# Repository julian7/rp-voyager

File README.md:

# Voyager keyboard with RP2354A

This repository contains the necessary files for manufacturing of a split keyboard with on-board RP2354A microcontroller.

Features:

- On-board RP2354A MCU (2MB flash) for each side
- USB-C connection for power, firmware update, and a separate USB-C for UART connection between the halves
- RGB matrix under each key
- Gateron KS-33 / Kailh Choc v1 / Kailh Choc v2 low-profile keyswitches
- 1.2mm top plate (mainly planning for KS-33)
- FreeCAD design for case and plate
- ZMK firmware with local build

Non-features:

- Wireless functionality
- No tooling for mass production beyond common PCB prototyping and hobbyist CNC/3D print.

## What is Voyager?

Voyager is a minimal, split keyboard by [ZSA Technology Labs](https://www.zsa.io/), the same company who was behind the now discontinued Planck EZ.

The original Voyager is using an STM32 MCU, with RGB matrix. It has 52 keys, and 52 LEDs.

## Project status

Experimental build is done:

Electronics are working well, but LED power consumption can exceed available resources. Please be aware that higher LED brightness settings can crash the firmware.

## Change notes

Version v1.0 has been built, but the left side is not usable:

- ROW0-ROW3 are not connected to the MCU
- missing trace between CONN_TX test pad and the side USB recepticle's TX line

The right side can be put to work, with a single design flaw:

- The eFuse is always disabled. As a solution, put a 1 MΩ resistor (I've used a 0805 package, but probably a 0603 would be better) between pin 1 and pin 2 of Q1 MOSFET.

In general, LED silk screen markings were unreadable, and the ones I've purchased had different pin numbering. I've placed them by following the traces instead.

As a minor detail, SMD encoders' holes are a bit too tight, a 0.1mm clearance is added. Some silkscreen markings were adjusted for readability and visibility.

Version v1.1: only left side has been ordered, as there are no significant upgrades on the right side.

Version v1.2 (PCB only): hours after ordering the PCB I found that the keyboard layout is slightly different on the right side. Since I've ordered a new series of the left half, I've updated the design for the right one. A mechanical plate design now contains a v1-specific right plate.

## Licensing

The contents of this project itself is licensed under [Creative Commons Attribution 4.0 International](LICENSE-CC-BY-4.0.txt), the underlying source code is licensed under [MIT license](LICENSE-MIT.txt), and the hardware / mechanical part is licensed under [CERN Open Hardware-Weakly reciprocal 2.0](LICENSE-CERN-OHL-W-2.0.txt).

I don't recommend any usage at this point, but I invite you to watch, to learn, and to laugh at my failures.

The original design is originated by ZSA Technology Labs, Inc. I can't stop being gratituous enough for all the things they've done.

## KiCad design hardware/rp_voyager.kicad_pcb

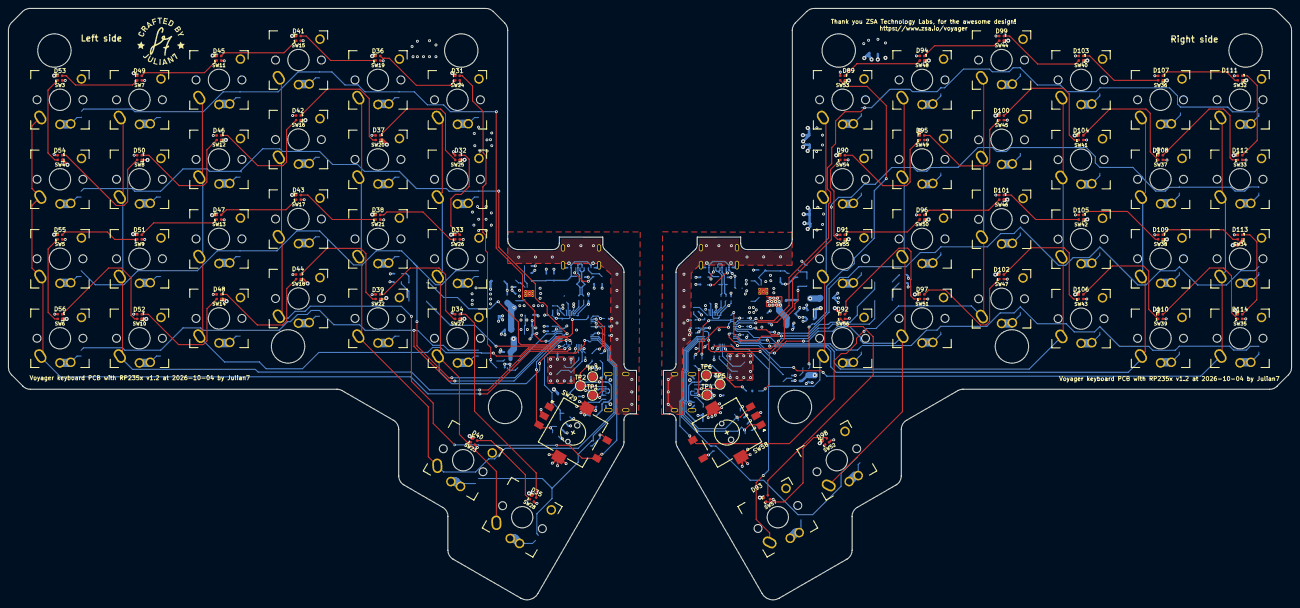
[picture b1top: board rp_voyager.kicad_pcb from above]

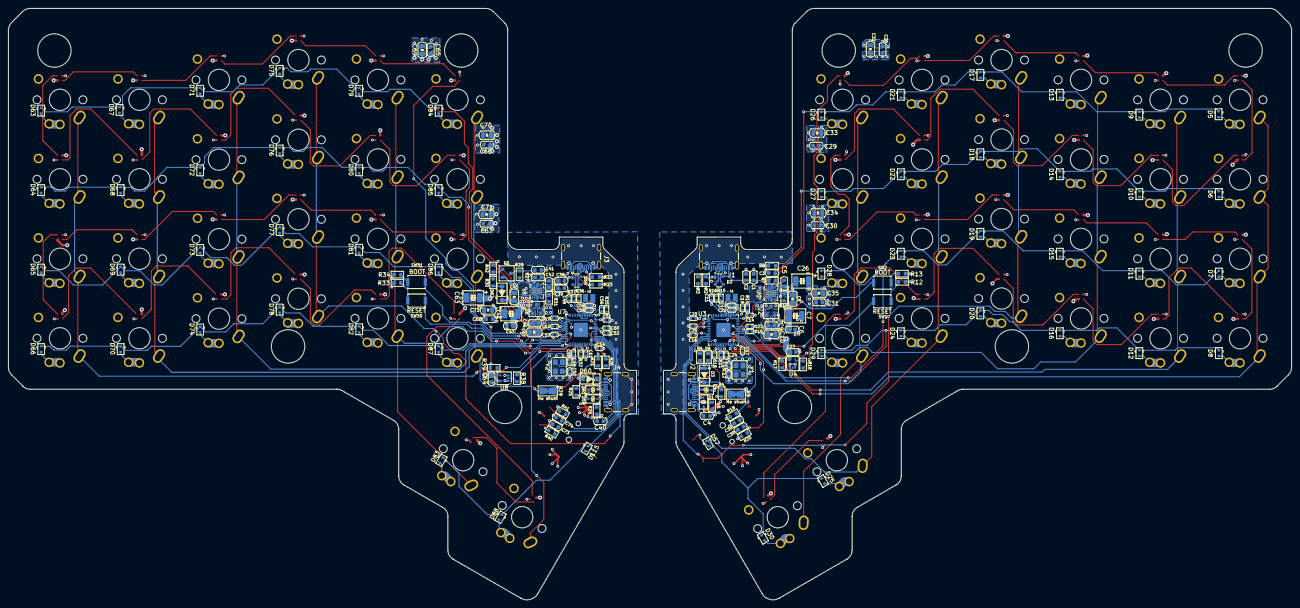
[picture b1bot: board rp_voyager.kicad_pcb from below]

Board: 4 copper layers, 307.5 x 141.7 mm, 317 parts (202 on the bottom side), 199 nets.

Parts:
C1, C6, C9, C27, C28, C29, C30, C31, C36, C37, C38, C43, C46, C64, C65, C66, C67, C68, C73, C74: 100n; C_0603_1608Metric
C2, C39: 10u; C_0603_1608Metric
C3, C4, C40, C41: 10n; C_0603_1608Metric
C5, C42: 1n; C_0603_1608Metric
C7, C26, C44, C63: 220u; CP_EIA-3528-21_Kemet-B
C8, C10, C32, C33, C34, C35, C45, C47, C69, C70, C71, C72: 10u; C_0805_2012Metric
C11, C14, C15, C16, C17, C18, C20, C23, C25, C48, C51, C52, C53, C54, C55, C57, C60, C62: 100n; C_0402_1005Metric
C12, C13, C49, C50: 15p; C_0402_1005Metric
C19, C21, C22, C24, C56, C58, C59, C61: 4.7u; C_0402_1005Metric
D1, D4, D58, D61: DESD5V0U1BA-7; D_SOD-323_TVS
D2, D59: PRTR5V0U2X; SOT-143
D3, D60: SZSMF5.0AT1G; D_SOD-123_Zener
D5, D6, D7, D8, D9, D10, D11, D12, D13, D14, D15, D16, D17, D18, D19, D20, D21, D22, D23, D24, D25, D26, D27, D28, D29, D30, D57, D63, D64, D65, D66, D67, D68, D69, D70, D71, D72, D73, D74, D75, D76, D77, D78, D79, D80, D81, D82, D83, D84, D85, D86, D87, D88, D115: 1N4148WT; D_SOD-523
D31, D32, D33, D34, D35, D36, D37, D38, D39, D40, D41, D42, D43, D44, D45, D46, D47, D48, D49, D50, D51, D52, D53, D54, D55, D56, D89, D90, D91, D92, D93, D94, D95, D96, D97, D98, D99, D100, D101, D102, D103, D104, D105, D106, D107, D108, D109, D110, D111, D112, D113, D114: SK6812 EC20; LED_SK6812_EC20_2x2mm
D62: B0520LW-7-F; D_SOD-123
J1, J3: INPUT USB; USB_C_Receptacle_GCT_USB4105-xx-A_16P_TopMnt_Horizontal
J2, J4: UART USB; USB_C_Receptacle_GCT_USB4105-xx-A_16P_TopMnt_Horizontal
L1, L2: AOTA-B201610S3R3-101-T; INDC2016X100N
PCB shape left1, PCB shape left2: PCB left
Q1: 2N7002; SOT-23
R1, R6, R21, R26: 220; R_0603_1608Metric
R2, R3, R4, R5, R22, R23, R24, R25: 5.1k; R_0603_1608Metric
R7, R19, R20, R27, R40, R41: 10k; R_0603_1608Metric
R8, R28, R30: 100k; R_0603_1608Metric
R9, R29: 0; R_1206_3216Metric_WireJumper
R10, R31: 0; R_0603_1608Metric
R11, R32: 1k; R_0402_1005Metric
R12, R13, R33, R34: 1k; R_0603_1608Metric
R14, R35: 33; R_0402_1005Metric
R15, R16, R36, R37: 27; R_0402_1005Metric
R17, R38: 22; R_0603_1608Metric
R18, R39: 47; R_0603_1608Metric
R42: 1M; R_0603_1608Metric
Realestateleft1, Realestateleft2: Realestate left
SW1, SW30: RESET; SW_Push_SPST_NO_Alps_SKRK
SW2, SW31: BOOTSEL; SW_Push_SPST_NO_Alps_SKRK
SW3, SW4, SW5, SW6, SW7, SW8, SW9, SW10, SW11, SW12, SW13, SW14, SW15, SW16, SW17, SW18, SW19, SW20, SW21, SW22, SW23, SW24, SW25, SW26, SW27, SW32, SW33, SW34, SW35, SW36, SW37, SW38, SW39, SW40, SW41, SW42, SW43, SW44, SW45, SW46, SW47, SW48, SW49, SW50, SW51, SW52, SW53, SW54, SW55, SW56: Key; Gateron-KS33-Solderable-1U
SW28, SW57: Key; Gateron-KS33-Solderable-1x1.5U
SW29, SW58: RotaryEncoder_Switch_MP; RotaryEncoder_Alps_EC11S-Switch_Vertical_H9mm
TP1, TP4: UART_TX; TestPoint_Pad_D2.0mm
TP2, TP5: UART_RX; TestPoint_Pad_D2.0mm
TP3, TP6: I2C 5V; TestPoint_Pad_D2.0mm
U1, U5: TPS259261; VSON-10-1EP_3x3mm_P0.5mm_EP1.65x2.4mm_ThermalVias
U2, U6: AP2125N-3.3TRG1; SOT-23
U3, U7: RP2354A; QFN-60-1EP_7x7mm_P0.4mm_EP3.4x3.4mm
U4, U8: 74HCT1G125GW; SOT-353_SC-70-5
Y1, Y2: 12MHz; Crystal_SMD_Abracon_ABM8G-4Pin_3.2x2.5mm
makersmark1: julian7_makers_mark

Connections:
/Left/Backlight RGB LEDs/RGB_DATA: R17.1, U3.37 (GPIO25)
/Left/Connector and Power/+3.3V: C9.1, C10.1, C11.1, C14.1, C15.1, C16.1, C17.1, C18.1, C20.1, C21.1, R14.1, R19.2, R20.2, U2.2 (OUT), U3.1 (IOVDD), U3.11 (IOVDD), U3.20 (IOVDD), U3.30 (IOVDD), U3.38 (IOVDD), U3.44 (ADC_AVDD), U3.45 (IOVDD), U3.49 (VREG_VIN), U3.53 (USB_OTP_VDD), U3.54 (QSPI_IOVDD)
/Left/Connector and Power/+5V: C6.1, C7.1, C8.1, C26.1, C27.1, C28.1, C29.1, C30.1, C31.1, C32.1, C33.1, C34.1, C35.1, D31.4 (VDD), D32.4 (VDD), D33.4 (VDD), D34.4 (VDD), D35.4 (VDD), D36.4 (VDD), D37.4 (VDD), D38.4 (VDD), D39.4 (VDD), D40.4 (VDD), D41.4 (VDD), D42.4 (VDD), D43.4 (VDD), D44.4 (VDD), D45.4 (VDD), D46.4 (VDD), D47.4 (VDD), D48.4 (VDD), D49.4 (VDD), D50.4 (VDD), D51.4 (VDD), D52.4 (VDD), D53.4 (VDD), D54.4 (VDD), D55.4 (VDD), D56.4 (VDD), R9.1, U1.6 (OUT), U1.7 (OUT), U1.8 (OUT), U2.3 (IN), U4.5 (VCC)
/Left/Connector and Power/CONN_CC1: J2.A5 (CC1), R4.1
/Left/Connector and Power/CONN_CC2: J2.B5 (CC2), R5.1
/Left/Connector and Power/CONN_RX: D4.2 (A), J2.A7 (D-), J2.B7 (D-), R6.1, TP2.1 (1_1)
/Left/Connector and Power/CONN_TX: D1.2 (A), J2.A6 (D+), J2.B6 (D+), R1.1, TP1.1 (1_1)
/Left/Connector and Power/CONN_VBUS: C4.1, D3.1 (K), J2.A4 (VBUS), J2.A9 (VBUS), J2.B4 (VBUS), J2.B9 (VBUS), R9.2, TP3.1 (1_1)
/Left/Connector and Power/UART_RX: R6.2, U3.3 (GPIO1)
/Left/Connector and Power/UART_TX: R1.2, U3.2 (GPIO0)
/Left/Connector and Power/USB_CC1: J1.A5 (CC1), R2.1
/Left/Connector and Power/USB_CC2: J1.B5 (CC2), R3.1
/Left/Connector and Power/USB_DN: D2.3 (I/O2), J1.A7 (D-), J1.B7 (D-), R15.1
/Left/Connector and Power/USB_DP: D2.2 (I/O1), J1.A6 (D+), J1.B6 (D+), R16.1
/Left/Connector and Power/VBUS: C1.1, C2.1, D2.4 (VCC), J1.A4 (VBUS), J1.A9 (VBUS), J1.B4 (VBUS), J1.B9 (VBUS), R7.2, U1.3 (VIN), U1.4 (VIN), U1.5 (VIN)
/Left/Encoder/CLK: C36.1, R19.1, SW29.A, U3.31 (GPIO19)
/Left/Encoder/DT: C37.1, R20.1, SW29.B, U3.32 (GPIO20)
/Left/Encoder/SW_COL: SW15.1, SW16.1, SW17.1, SW18.1, SW29.S1, U3.12 (GPIO8)
/Left/Encoder/SW_ROW: D25.1 (K), D30.1 (K), D57.1 (K), U3.13 (GPIO9)
/Left/Key Matrix/COL0: SW3.1, SW4.1, SW5.1, SW6.1, U3.27 (GPIO16)
/Left/Key Matrix/COL1: SW7.1, SW8.1, SW9.1, SW10.1, U3.28 (GPIO17)
/Left/Key Matrix/COL2: SW11.1, SW12.1, SW13.1, SW14.1, U3.29 (GPIO18)
/Left/Key Matrix/COL4: SW19.1, SW20.1, SW21.1, SW22.1, SW23.1, U3.14 (GPIO10)
/Left/Key Matrix/COL5: SW24.1, SW25.1, SW26.1, SW27.1, SW28.1, U3.15 (GPIO11)
/Left/Key Matrix/ROW0: D5.1 (K), D9.1 (K), D13.1 (K), D17.1 (K), D21.1 (K), D26.1 (K), U3.36 (GPIO24)
/Left/Key Matrix/ROW1: D6.1 (K), D10.1 (K), D14.1 (K), D18.1 (K), D22.1 (K), D27.1 (K), U3.35 (GPIO23)
/Left/Key Matrix/ROW2: D7.1 (K), D11.1 (K), D15.1 (K), D19.1 (K), D23.1 (K), D28.1 (K), U3.34 (GPIO22)
/Left/Key Matrix/ROW3: D8.1 (K), D12.1 (K), D16.1 (K), D20.1 (K), D24.1 (K), D29.1 (K), U3.33 (GPIO21)
/Left/MCU/+1.1V: C22.1, C23.1, C24.1, C25.1, L1.1, U3.6 (DVDD), U3.23 (DVDD), U3.39 (DVDD), U3.50 (VREG_FB)
/Right/Backlight RGB LEDs (copy)/RGB_DATA: R38.1, U7.37 (GPIO25)
/Right/Connector and Power/+3.3V: C46.1, C47.1, C48.1, C51.1, C52.1, C53.1, C54.1, C55.1, C57.1, C58.1, R35.1, R40.2, R41.2, U6.2 (OUT), U7.1 (IOVDD), U7.11 (IOVDD), U7.20 (IOVDD), U7.30 (IOVDD), U7.38 (IOVDD), U7.44 (ADC_AVDD), U7.45 (IOVDD), U7.49 (VREG_VIN), U7.53 (USB_OTP_VDD), U7.54 (QSPI_IOVDD)
/Right/Connector and Power/+5V: C43.1, C44.1, C45.1, C63.1, C64.1, C65.1, C66.1, C67.1, C68.1, C69.1, C70.1, C71.1, C72.1, D62.1 (K), D89.4 (VDD), D90.4 (VDD), D91.4 (VDD), D92.4 (VDD), D93.4 (VDD), D94.4 (VDD), D95.4 (VDD), D96.4 (VDD), D97.4 (VDD), D98.4 (VDD), D99.4 (VDD), D100.4 (VDD), D101.4 (VDD), D102.4 (VDD), D103.4 (VDD), D104.4 (VDD), D105.4 (VDD), D106.4 (VDD), D107.4 (VDD), D108.4 (VDD), D109.4 (VDD), D110.4 (VDD), D111.4 (VDD), D112.4 (VDD), D113.4 (VDD), D114.4 (VDD), U5.6 (OUT), U5.7 (OUT), U5.8 (OUT), U6.3 (IN), U8.5 (VCC)
/Right/Connector and Power/CONN_CC1: J4.A5 (CC1), R24.1
/Right/Connector and Power/CONN_CC2: J4.B5 (CC2), R25.1
/Right/Connector and Power/CONN_RX: D61.2 (A), J4.A6 (D+), J4.B6 (D+), R26.1, TP5.1 (1_1)
/Right/Connector and Power/CONN_TX: D58.2 (A), J4.A7 (D-), J4.B7 (D-), R21.1, TP4.1 (1_1)
/Right/Connector and Power/CONN_VBUS: C40.1, D60.1 (K), J4.A4 (VBUS), J4.A9 (VBUS), J4.B4 (VBUS), J4.B9 (VBUS), R29.2, TP6.1 (1_1)
/Right/Connector and Power/UART_RX: R26.2, U7.3 (GPIO1)
/Right/Connector and Power/UART_TX: R21.2, U7.2 (GPIO0)
/Right/Connector and Power/USB_CC1: J3.A5 (CC1), R22.1
/Right/Connector and Power/USB_CC2: J3.B5 (CC2), R23.1
/Right/Connector and Power/USB_DN: D59.3 (I/O2), J3.A7 (D-), J3.B7 (D-), R36.1
/Right/Connector and Power/USB_DP: D59.2 (I/O1), J3.A6 (D+), J3.B6 (D+), R37.1
/Right/Connector and Power/VBUS: C38.1, C39.1, D59.4 (VCC), J3.A4 (VBUS), J3.A9 (VBUS), J3.B4 (VBUS), J3.B9 (VBUS), R27.2, U5.3 (VIN), U5.4 (VIN), U5.5 (VIN)
/Right/Encoder (copy)/CLK: C73.1, R40.1, SW58.A, U7.32 (GPIO20)
/Right/Encoder (copy)/DT: C74.1, R41.1, SW58.B, U7.31 (GPIO19)
/Right/Encoder (copy)/SW_COL: SW44.1, SW45.1, SW46.1, SW47.1, SW58.S1, U7.34 (GPIO22)
/Right/Encoder (copy)/SW_ROW: D83.1 (K), D88.1 (K), D115.1 (K), U7.33 (GPIO21)
/Right/Key Matrix (copy)/COL0: SW32.1, SW33.1, SW34.1, SW35.1, U7.10 (GPIO7)
/Right/Key Matrix (copy)/COL1: SW36.1, SW37.1, SW38.1, SW39.1, U7.12 (GPIO8)
/Right/Key Matrix (copy)/COL2: SW40.1, SW41.1, SW42.1, SW43.1, U7.13 (GPIO9)
/Right/Key Matrix (copy)/COL4: SW48.1, SW49.1, SW50.1, SW51.1, SW52.1, U7.15 (GPIO11)
/Right/Key Matrix (copy)/COL5: SW53.1, SW54.1, SW55.1, SW56.1, SW57.1, U7.16 (GPIO12)
/Right/Key Matrix (copy)/ROW0: D63.1 (K), D67.1 (K), D71.1 (K), D75.1 (K), D79.1 (K), D84.1 (K), U7.4 (GPIO2)
/Right/Key Matrix (copy)/ROW1: D64.1 (K), D68.1 (K), D72.1 (K), D76.1 (K), D80.1 (K), D85.1 (K), U7.5 (GPIO3)
/Right/Key Matrix (copy)/ROW2: D65.1 (K), D69.1 (K), D73.1 (K), D77.1 (K), D81.1 (K), D86.1 (K), U7.7 (GPIO4)
/Right/Key Matrix (copy)/ROW3: D66.1 (K), D70.1 (K), D74.1 (K), D78.1 (K), D82.1 (K), D87.1 (K), U7.8 (GPIO5)
/Right/MCU (copy)/+1.1V: C59.1, C60.1, C61.1, C62.1, L2.1, U7.6 (DVDD), U7.23 (DVDD), U7.39 (DVDD), U7.50 (VREG_FB)
GND: C1.2, C2.2, C3.2, C4.2, C5.2, C6.2, C7.2, C8.2, C9.2, C10.2, C11.2, C12.1, C13.1, C14.2, C15.2, C16.2, C17.2, C18.2, C19.1, C20.2, C21.2, C22.2, C23.2, C24.2, C25.2, C26.2, C27.2, C28.2, C29.2, C30.2, C31.2, C32.2, C33.2, C34.2, C35.2, C36.2, C37.2, C38.2, C39.2, C40.2, C41.2, C42.2, C43.2, C44.2, C45.2, C46.2, C47.2, C48.2, C49.1, C50.1, C51.2, C52.2, C53.2, C54.2, C55.2, C56.1, C57.2, C58.2, C59.2, C60.2, C61.2, C62.2, C63.2, C64.2, C65.2, C66.2, C67.2, C68.2, C69.2, C70.2, C71.2, C72.2, C73.2, C74.2, D1.1 (K), D2.1 (GND), D3.2 (A), D4.1 (K), D31.2 (VSS), D32.2 (VSS), D33.2 (VSS), D34.2 (VSS), D35.2 (VSS), D36.2 (VSS), D37.2 (VSS), D38.2 (VSS), D39.2 (VSS), D40.2 (VSS), D41.2 (VSS), D42.2 (VSS), D43.2 (VSS), D44.2 (VSS), D45.2 (VSS), D46.2 (VSS), D47.2 (VSS), D48.2 (VSS), D49.2 (VSS), D50.2 (VSS), D51.2 (VSS), D52.2 (VSS), D53.2 (VSS), D54.2 (VSS), D55.2 (VSS), D56.2 (VSS), D58.1 (K), D59.1 (GND), D60.2 (A), D61.1 (K), D89.2 (VSS), D90.2 (VSS), D91.2 (VSS), D92.2 (VSS), D93.2 (VSS), D94.2 (VSS), D95.2 (VSS), D96.2 (VSS), D97.2 (VSS), D98.2 (VSS), D99.2 (VSS), D100.2 (VSS), D101.2 (VSS), D102.2 (VSS), D103.2 (VSS), D104.2 (VSS), D105.2 (VSS), D106.2 (VSS), D107.2 (VSS), D108.2 (VSS), D109.2 (VSS), D110.2 (VSS), D111.2 (VSS), D112.2 (VSS), D113.2 (VSS), D114.2 (VSS), J1.A1 (GND), J1.A12 (GND), J1.B1 (GND), J1.B12 (GND), J1.SH (SHIELD), J2.A1 (GND), J2.A12 (GND), J2.B1 (GND), J2.B12 (GND), J2.SH (SHIELD), J3.A1 (GND), J3.A12 (GND), J3.B1 (GND), J3.B12 (GND), J3.SH (SHIELD), J4.A1 (GND), J4.A12 (GND), J4.B1 (GND), J4.B12 (GND), J4.SH (SHIELD), Q1.2 (S), R2.2, R3.2, R4.2, R5.2, R8.1, R10.1, R12.1, R13.1, R22.2, R23.2, R24.2, R25.2, R28.1, R31.1, R33.1, R34.1, R42.2, SW29.C, SW29.MP, SW58.C, SW58.MP, U1.11 (GND), U2.1, U3.47 (VREG_PGND), U3.61 (GND), U4.1, U4.3 (GND), U5.11 (GND), U6.1, U7.47 (VREG_PGND), U7.61 (GND), U8.1, U8.3 (GND), Y1.2 (G), Y1.4 (G), Y2.2 (G), Y2.4 (G)
unnamed: C13.2, R11.1, Y1.3
unnamed: C50.2, R32.1, Y2.3
unnamed: D5.2 (A), SW3.2
unnamed: D6.2 (A), SW4.2
unnamed: D7.2 (A), SW5.2
unnamed: D8.2 (A), SW6.2
unnamed: D9.2 (A), SW7.2
unnamed: D10.2 (A), SW8.2
unnamed: D11.2 (A), SW9.2
unnamed: D12.2 (A), SW10.2
unnamed: D13.2 (A), SW11.2
unnamed: D14.2 (A), SW12.2
unnamed: D15.2 (A), SW13.2
unnamed: D16.2 (A), SW14.2
unnamed: D17.2 (A), SW15.2
unnamed: D18.2 (A), SW16.2
unnamed: D19.2 (A), SW17.2
unnamed: D20.2 (A), SW18.2
unnamed: D21.2 (A), SW19.2
unnamed: D22.2 (A), SW20.2
unnamed: D23.2 (A), SW21.2
unnamed: D24.2 (A), SW22.2
unnamed: D25.2 (A), SW23.2
unnamed: D26.2 (A), SW24.2
unnamed: D27.2 (A), SW25.2
unnamed: D28.2 (A), SW26.2
unnamed: D29.2 (A), SW27.2
unnamed: D30.2 (A), SW28.2
unnamed: D31.3 (DIN), R18.2
unnamed: D31.1 (DOUT), D36.3 (DIN)
unnamed: D32.3 (DIN), D37.1 (DOUT)
unnamed: D32.1 (DOUT), D33.3 (DIN)
unnamed: D33.1 (DOUT), D38.3 (DIN)
unnamed: D34.3 (DIN), D39.1 (DOUT)
unnamed: D34.1 (DOUT), D35.3 (DIN)
unnamed: D35.1 (DOUT), D40.3 (DIN)
unnamed: D36.1 (DOUT), D41.3 (DIN)
unnamed: D37.3 (DIN), D42.1 (DOUT)
unnamed: D38.1 (DOUT), D43.3 (DIN)
unnamed: D39.3 (DIN), D44.1 (DOUT)
unnamed: D41.1 (DOUT), D45.3 (DIN)
unnamed: D42.3 (DIN), D46.1 (DOUT)
unnamed: D43.1 (DOUT), D47.3 (DIN)
unnamed: D44.3 (DIN), D48.1 (DOUT)
unnamed: D45.1 (DOUT), D49.3 (DIN)
unnamed: D46.3 (DIN), D50.1 (DOUT)
unnamed: D47.1 (DOUT), D51.3 (DIN)
unnamed: D48.3 (DIN), D52.1 (DOUT)
unnamed: D49.1 (DOUT), D53.3 (DIN)
unnamed: D50.3 (DIN), D54.1 (DOUT)
unnamed: D51.1 (DOUT), D55.3 (DIN)
unnamed: D52.3 (DIN), D56.1 (DOUT)
unnamed: D53.1 (DOUT), D54.3 (DIN)
unnamed: D55.1 (DOUT), D56.3 (DIN)
unnamed: D57.2 (A), SW29.S2
unnamed: D62.2 (A), R29.1, R30.1
unnamed: D63.2 (A), SW32.2
unnamed: D64.2 (A), SW33.2
unnamed: D65.2 (A), SW34.2
unnamed: D66.2 (A), SW35.2
unnamed: D67.2 (A), SW36.2
unnamed: D68.2 (A), SW37.2
unnamed: D69.2 (A), SW38.2
unnamed: D70.2 (A), SW39.2
unnamed: D71.2 (A), SW40.2
unnamed: D72.2 (A), SW41.2
unnamed: D73.2 (A), SW42.2
unnamed: D74.2 (A), SW43.2
unnamed: D75.2 (A), SW44.2
unnamed: D76.2 (A), SW45.2
unnamed: D77.2 (A), SW46.2
unnamed: D78.2 (A), SW47.2
unnamed: D79.2 (A), SW48.2
unnamed: D80.2 (A), SW49.2
unnamed: D81.2 (A), SW50.2
unnamed: D82.2 (A), SW51.2
unnamed: D83.2 (A), SW52.2
unnamed: D84.2 (A), SW53.2
unnamed: D85.2 (A), SW54.2
unnamed: D86.2 (A), SW55.2
unnamed: D87.2 (A), SW56.2
unnamed: D88.2 (A), SW57.2
unnamed: D89.3 (DIN), R39.2
unnamed: D89.1 (DOUT), D94.3 (DIN)
unnamed: D90.3 (DIN), D95.1 (DOUT)
unnamed: D90.1 (DOUT), D91.3 (DIN)
unnamed: D91.1 (DOUT), D96.3 (DIN)
unnamed: D92.3 (DIN), D97.1 (DOUT)
unnamed: D92.1 (DOUT), D93.3 (DIN)
unnamed: D93.1 (DOUT), D98.3 (DIN)
unnamed: D94.1 (DOUT), D99.3 (DIN)
unnamed: D100.3 (DIN), D104.1 (DOUT)
unnamed: D95.3 (DIN), D100.1 (DOUT)
unnamed: D96.1 (DOUT), D101.3 (DIN)
unnamed: D101.1 (DOUT), D105.3 (DIN)
unnamed: D102.3 (DIN), D106.1 (DOUT)
unnamed: D97.3 (DIN), D102.1 (DOUT)
unnamed: D99.1 (DOUT), D103.3 (DIN)
unnamed: D103.1 (DOUT), D107.3 (DIN)
unnamed: D104.3 (DIN), D108.1 (DOUT)
unnamed: D105.1 (DOUT), D109.3 (DIN)
unnamed: D106.3 (DIN), D110.1 (DOUT)
unnamed: D107.1 (DOUT), D111.3 (DIN)
unnamed: D108.3 (DIN), D112.1 (DOUT)
unnamed: D109.1 (DOUT), D113.3 (DIN)
unnamed: D110.3 (DIN), D114.1 (DOUT)
unnamed: D111.1 (DOUT), D112.3 (DIN)
unnamed: D113.1 (DOUT), D114.3 (DIN)
unnamed: D115.2 (A), SW58.S2
unnamed: C41.1, Q1.3 (D), R27.1, R28.2, U5.2 (EN/UVLO)
unnamed: Q1.1 (G), R30.2, R42.1
unnamed: R12.2, SW1.1
unnamed: R13.2, SW2.1
unnamed: R17.2, U4.2
unnamed: R18.1, U4.4
unnamed: R33.2, SW30.1
unnamed: R34.2, SW31.1
unnamed: R38.2, U8.2
unnamed: R39.1, U8.4
unnamed: C3.1, R7.1, R8.2, U1.2 (EN/UVLO)
unnamed: R10.2, U1.10 (ILIM)
unnamed: C5.1, U1.1 (dV/dT)
unnamed: SW1.2, U3.26 (RUN)
unnamed: R15.2, U3.51 (USB_DM)
unnamed: R16.2, U3.52 (USB_DP)
unnamed: C19.2, R14.2, U3.46 (VREG_AVDD)
unnamed: L1.2, U3.48 (VREG_LX)
unnamed: C12.2, U3.21 (XIN), Y1.1
unnamed: R11.2, U3.22 (XOUT)
unnamed: SW2.2, U3.60 (~QSPI_SS)
unnamed: R31.2, U5.10 (ILIM)
unnamed: C42.1, U5.1 (dV/dT)
unnamed: SW30.2, U7.26 (RUN)
unnamed: R36.2, U7.51 (USB_DM)
unnamed: R37.2, U7.52 (USB_DP)
unnamed: C56.2, R35.2, U7.46 (VREG_AVDD)
unnamed: L2.2, U7.48 (VREG_LX)
unnamed: C49.2, U7.21 (XIN), Y2.1
unnamed: R32.2, U7.22 (XOUT)
unnamed: SW31.2, U7.60 (~QSPI_SS)

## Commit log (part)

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2026-05-24 initial
2026-05-24 split definition with duplex UART
2026-05-24 add rotary encoder to firmware
2026-05-24 separate left/right part design, schematic
2026-05-24 zmk firmware config
2026-05-24 buildable firmware
2026-05-24 encoder to schematic
2026-05-24 document ZMK local toolchain install
2026-06-16 electronics
2026-06-17 rendered electronics pics
